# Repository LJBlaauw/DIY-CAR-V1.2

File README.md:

# DIY Robot CAR

**Dit project is begonnen met het idee van mijn zwager om een robot karretje te maken**
Ik heb zelf een achtergrond in ontwikkeling van elektronica (microcontrollers, vermogens-elektronica en audio).
Voor mijn zwager was dit onbekend gebied dus zoals wel vaker gebeurt heb ik mijn hulp aangeboden.
Voor de ontwikkeling is er gebruik gemaakt van opensource software. Als OS heb ik Linux Fedora 44 desktop KDE plasma gebruikt.
De uitdaging is om het karretje autonoom deze handelingen te laten uitvoeren, vooral het real-time karakter hierbij is een uitdaging.
Eerst hebben we alles op een breadboardje gebouwd. Dit was niet erg succesvol omdat de bedrading vaak geen betrouwbare verbindingen gaf.
Ook was de keuze van het type stappenmotor (unipolair) en servo's niet toereikend (te licht, te veel mechanische speling)
Dus versie nul is geüpdatet naar versie 1 met bipolaire stappenmotoren en drivers, MG996 servo's met metalen tandwielen.
Om dit te kunnen monteren zijn er diverse onderdelen 3D-geprint. 
In versie 1 was het grootste deel van de mechanica opgebouwd uit plaatmateriaal en aluminium profielen.
In versie 2 is er een elektronisch kompas en versnellingsopnemer toegevoegd. Ook is de grijper principieel gewijzigd en is zoveel als mogelijk 3D-geprint.

De eerste vragen die beantwoord moesten worden waren:
 1. Wat is de scope van het project (wat moet het robot karretje doen)
 2. Wat is goed online verkrijgbaar 
 3. Welke materialen gaan we gebruiken (motoren en sensoren)
 4. Wat voor software gaan we gebruiken om de besturing mogelijk te maken.
 5. presentatie van status en meet gegevens
 6. Ontwikkel gereedschappen en omgeving
 
1. **Scope: Het robot karretje moet autonoom zoeken naar een lichtbron en daar een voorwerp pakken en naar het vertrekpunt brengen**

2. **verkrijgbaarheid:**
 1. Bij diverse hobby winkels, amazon en aliexpress konden we alles wel vinden.
 
3. **Materialen**
 1. *Motoren:*
    1. Twee onafhankelijk te besturen stappenmotoren voor de voortbeweging.
    2. Drie onafhankelijk te besturen servomotoren voor de robotarm en grijper.
    *Sensoren:*
    1. Ultrasoonsensor om de afstand van de kar tot het object te meten.
    2. Twee licht gevoelige weerstanden om de richting van de lichtbron te vinden.
    3. We hebben als Microcontroller gekozen voor de RP2040 van Raspberry Pi, in versie 2 de RP2350W.
    4. Als optie een kompas/versnellings opnemer.
    5. Als optie een wifi koppeling met een websocket om sensor data te lezen en opdragten te geven.
    
 4. **Programmeertaal**
    Voor de programmeertaal hebben we gekozen voor Micropython dit is eenvoudiger te leren dan C/C++.
    Het voordeel is dat er niet vertaald hoeft te worden en er veel kant en klare bibliotheek componenten ingebouwd zijn.
    Om een goed real-time werkend systeem te krijgen zijn er wel een aantal uitdagingen.
    Aangezien Micropython een interpreter is loopt dit een factor 100 langzamer dan C.
    Er zijn een aantal mogelijkheden om de realtime eigenschappen te optimaliseren.
    1. Gebruik maken van de in de microcontroller geïntegreerde PIO-statemachines.
    2. De Software modules (werkbelasting) te verdelen over de twee CPU cores
    3. eventueel gebruik maken van de coöperatieve multitasking (asyncio).
    
5. **Presentatie**
    Als presentatie hebben we als status melding een meerkleuren LED en een oled display van 128x64 dots.
    Met versie twee hebben we gekozen voor de RP2350W. Deze heeft 2 M33 i.p.v de M0 kernen.
    Met deze processor update is het rekenen aan de kompas/versnellings veel sneller,
    ook is met een websocket remote besturing/uitlezing mogelijk. 
    Verder zijn er twee ledjes die de 5V en 3.3V signaleren.
    Hierbij is ook de REPL van de IDE gereedschappen aanwezig om met print opdrachten informatie te tonen.
    
6. **Ontwikkelgereedschappen**
    Voor het ontwerpen en produceren van de printplaat voor de elektronica maak ik gebruik van:
    1. Schema en layout: KiCAD (nu versie 10.4), FlatCAM Gerber naar Gcode, CNC machine een geüpgrade 3018 met GRBLHAL controller.
    2. Mechanisch ontwerp: FreeCAD voor 3D parametrische modellen en een Prusa MK4 3D-printer.
    3. Software ontwikkel omgeving: IDE VSCODE met micropico-extensie en AI claude 4.6 chat.
    4. Thonny IDE simpelere ontwikkelomgeving dan VSCODE.

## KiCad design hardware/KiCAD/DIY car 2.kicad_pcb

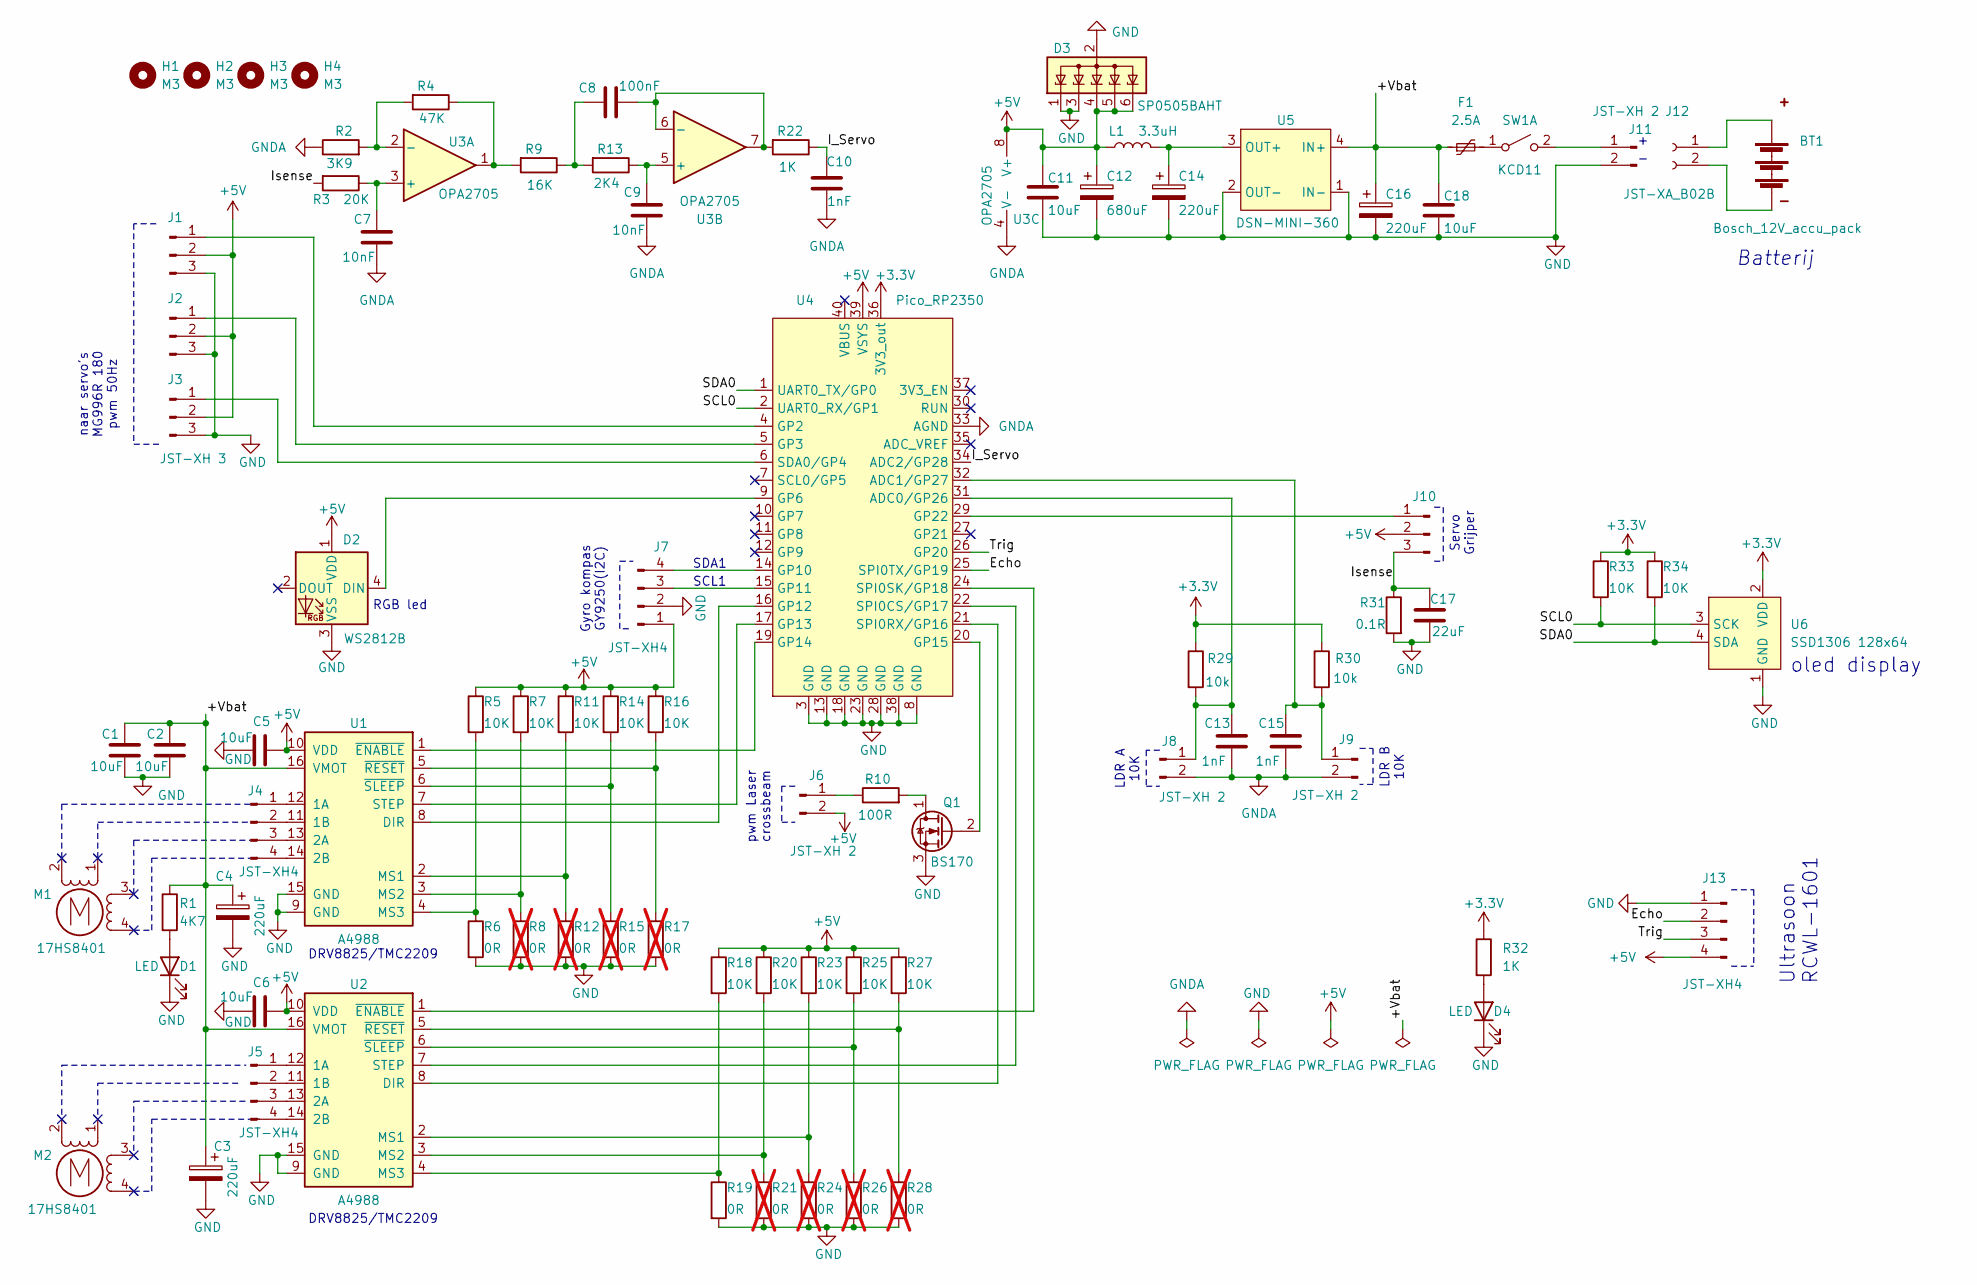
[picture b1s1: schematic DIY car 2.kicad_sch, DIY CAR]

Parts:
BT1: Bosch_12V_accu_pack; batterij houder bosch
C1, C2, C5, C6, C11, C18: 10uF; C_1206_3216Metric_Pad1.33x1.80mm_HandSolder
C3, C4, C14, C16: 220uF; CP_Radial_D6.3mm_P2.50mm
C7, C9: 10nF; C_1206_3216Metric_Pad1.33x1.80mm_HandSolder
C8: 100nF; C_1206_3216Metric_Pad1.33x1.80mm_HandSolder
C10, C13, C15: 1nF; C_1206_3216Metric_Pad1.33x1.80mm_HandSolder
C12: 680uF; CP_Radial_D8.0mm_P3.50mm
C17: 22uF; C_1210_3225Metric_Pad1.33x2.70mm_HandSolder
D1, D4: LED; LED_D3.0mm
D2: WS2812B; LED_WS2812B_PLCC4_5.0x5.0mm_P3.2mm
D3: SP0505BAHT; SOT-23-6
F1: 2.5A; Fuse_Bourns_MF-RG300
H1, H2, H3, H4: M3; MountingHole_3.5mm
J1, J2, J3, J10: JST-XH 3; JST_XH_B3B-XH-A_1x03_P2.50mm_Vertical
J4, J5, J7, J13: JST-XH4; JST_XH_B4B-XH-A_1x04_P2.50mm_Vertical
J6, J8, J9, J11: JST-XH 2; JST_XH_B2B-XH-AM_1x02_P2.50mm_Vertical_CNC
J12: JST-XA_B02B; JST_XA_B02B-XASK-1-A_1x02_P2.50mm_Vertical
L1: 3.3uH; L_APV_ANR6045
M1, M2: 17HS8401
Q1: BS170; TO-92_Inline
R1: 4K7; R_1206_3216Metric_Pad1.30x1.75mm_HandSolder
R2: 3K9; R_1206_3216Metric_Pad1.30x1.75mm_HandSolder
R3: 20K; R_1206_3216Metric_Pad1.30x1.75mm_HandSolder
R4: 47K; R_1206_3216Metric_Pad1.30x1.75mm_HandSolder
R5, R7, R11, R14, R16, R18, R20, R23, R25, R27, R33, R34: 10K; R_1206_3216Metric_Pad1.30x1.75mm_HandSolder
R6, R19: 0R; R_1206_3216Metric_Pad1.30x1.75mm_HandSolder
R8, R12, R15, R17, R21, R24, R26, R28: 0R; R_1206_3216Metric_Pad1.30x1.75mm_HandSolder; not fitted
R9: 16K; R_1206_3216Metric_Pad1.30x1.75mm_HandSolder
R10: 100R; R_1206_3216Metric_Pad1.30x1.75mm_HandSolder
R13: 2K4; R_1206_3216Metric_Pad1.30x1.75mm_HandSolder
R22, R32: 1K; R_1206_3216Metric_Pad1.30x1.75mm_HandSolder
R29, R30: 10k; R_1206_3216Metric_Pad1.30x1.75mm_HandSolder
R31: 0.1R; R_1020_2550Metric_Pad1.33x5.20mm_HandSolder
SW1: KCD11
U1, U2: A4988
U3: OPA2705; DIP-8_W7.62mm_Socket_LongPads
U4: Pico_RP2350; DIP-40_700mil
U5: DSN-MINI-360
U6: SSD1306 128x64; OLED 0.96 I2C

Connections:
+3.3V: R29.1, R30.1, R32.1, R33.1, R34.1, U4.36 (3V3_out), U6.2 (VDD)
+5V: C5.2, C6.2, C11.2, C12.1, D2.1 (VDD), D3.4 (K), D3.5 (K), D3.6 (K), J1.2, J2.2, J3.2, J6.2, J7.1, J10.2, J13.4, L1.1, R5.1, R7.1, R11.1, R14.1, R16.1, R18.1, R20.1, R23.1, R25.1, R27.1, U1.10 (VDD), U2.10 (VDD), U3.8 (V+), U4.39 (VSYS)
/+Vbat: C1.2, C2.2, C3.1, C4.1, C16.1, C18.2, F1.1, R1.1, U1.16 (VMOT), U2.16 (VMOT), U5.4 (IN+)
/Echo: J13.2, U4.25 (SPI0TX/GP19)
/I_Servo: C10.2, R22.1, U4.34 (ADC2/GP28)
/Isense: C17.1, J10.3, R3.2, R31.1
/SCL0: R33.2, U4.2 (UART0_RX/GP1), U6.3 (SCK)
/SDA0: R34.2, U4.1 (UART0_TX/GP0), U6.4 (SDA)
/Trig: J13.3, U4.26 (GP20)
GND: C1.1, C2.1, C3.2, C4.2, C5.1, C6.1, C11.1, C12.2, C14.2, C16.2, C17.2, C18.1, D1.1 (K), D2.3 (VSS), D3.1 (K), D3.2 (A), D3.3 (K), D4.1 (K), J1.3, J2.3, J3.3, J7.2, J11.2, J13.1, Q1.3 (S), R6.2, R8.2, R12.2, R15.2, R17.2, R19.2, R21.2, R24.2, R26.2, R28.2, R31.2, U1.9 (GND), U1.15 (GND), U2.9 (GND), U2.15 (GND), U4.3 (GND), U4.8 (GND), U4.13 (GND), U4.18 (GND), U4.23 (GND), U4.28 (GND), U4.38 (GND), U5.1 (IN-), U5.2 (OUT-), U6.1 (GND)
GNDA: C7.1, C9.1, C10.1, C13.1, C15.1, J8.2, J9.2, R2.1, U3.4 (V-), U4.33 (AGND)
unnamed: BT1.1 (+), J12.1
unnamed: BT1.2 (-), J12.2
unnamed: C8.1, R9.1, R13.2
unnamed: D1.2 (A), R1.2
unnamed: D2.4 (DIN), U4.9 (GP6)
unnamed: D4.2 (A), R32.2
unnamed: J1.1, U4.4 (GP2)
unnamed: J2.1, U4.5 (GP3)
unnamed: J3.1, U4.6 (SDA0/GP4)
unnamed: J4.1, U1.12 (1A)
unnamed: J4.2, U1.11 (1B)
unnamed: J4.3, U1.13 (2A)
unnamed: J4.4, U1.14 (2B)
unnamed: J5.1, U2.12 (1A)
unnamed: J5.2, U2.11 (1B)
unnamed: J5.3, U2.13 (2A)
unnamed: J5.4, U2.14 (2B)
unnamed: J6.1, R10.1
unnamed: J7.3, U4.15 (GP11)
unnamed: J7.4, U4.14 (GP10)
unnamed: C13.2, J8.1, R29.2, U4.31 (ADC0/GP26)
unnamed: C15.2, J9.1, R30.2, U4.32 (ADC1/GP27)
unnamed: J10.1, U4.29 (GP22)
unnamed: J11.1, SW1.2 (B)
unnamed: Q1.1 (D), R10.2
unnamed: Q1.2 (G), U4.20 (GP15)
unnamed: R4.1, R9.2, U3.1
unnamed: F1.2, SW1.1 (A)
unnamed: U1.8 (DIR), U4.16 (GP12)
unnamed: R11.2, R12.1, U1.2 (MS1)
unnamed: R7.2, R8.1, U1.3 (MS2)
unnamed: R5.2, R6.1, U1.4 (MS3)
unnamed: U1.7 (STEP), U4.17 (GP13)
unnamed: U1.1 (~ENABLE), U4.19 (GP14)
unnamed: R16.2, R17.1, U1.5 (~RESET)
unnamed: R14.2, R15.1, U1.6 (~SLEEP)
unnamed: U2.8 (DIR), U4.21 (SPI0RX/GP16)
unnamed: R23.2, R24.1, U2.2 (MS1)
unnamed: R20.2, R21.1, U2.3 (MS2)
unnamed: R18.2, R19.1, U2.4 (MS3)
unnamed: U2.7 (STEP), U4.22 (SPI0CS/GP17)
unnamed: U2.1 (~ENABLE), U4.24 (SPI0SK/GP18)
unnamed: R27.2, R28.1, U2.5 (~RESET)
unnamed: R25.2, R26.1, U2.6 (~SLEEP)
unnamed: C7.2, R3.1, U3.3 (+)
unnamed: R2.2, R4.2, U3.2 (-)
unnamed: C9.2, R13.1, U3.5 (+)
unnamed: C8.2, R22.2, U3.6 (-), U3.7
unnamed: C14.1, L1.2, U5.3 (OUT+)

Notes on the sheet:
oled display
LDR B 10K
DRV8825/TMC2209
SCL1
pwm Laser crossbeam
Ultrasoon RCWL-1601
Gyro kompas GY9250(I2C)
naar servo's MG996R 180 pwm 50Hz
RGB led
SDA1
Servo Grijper
LDR A 10K
Batterij

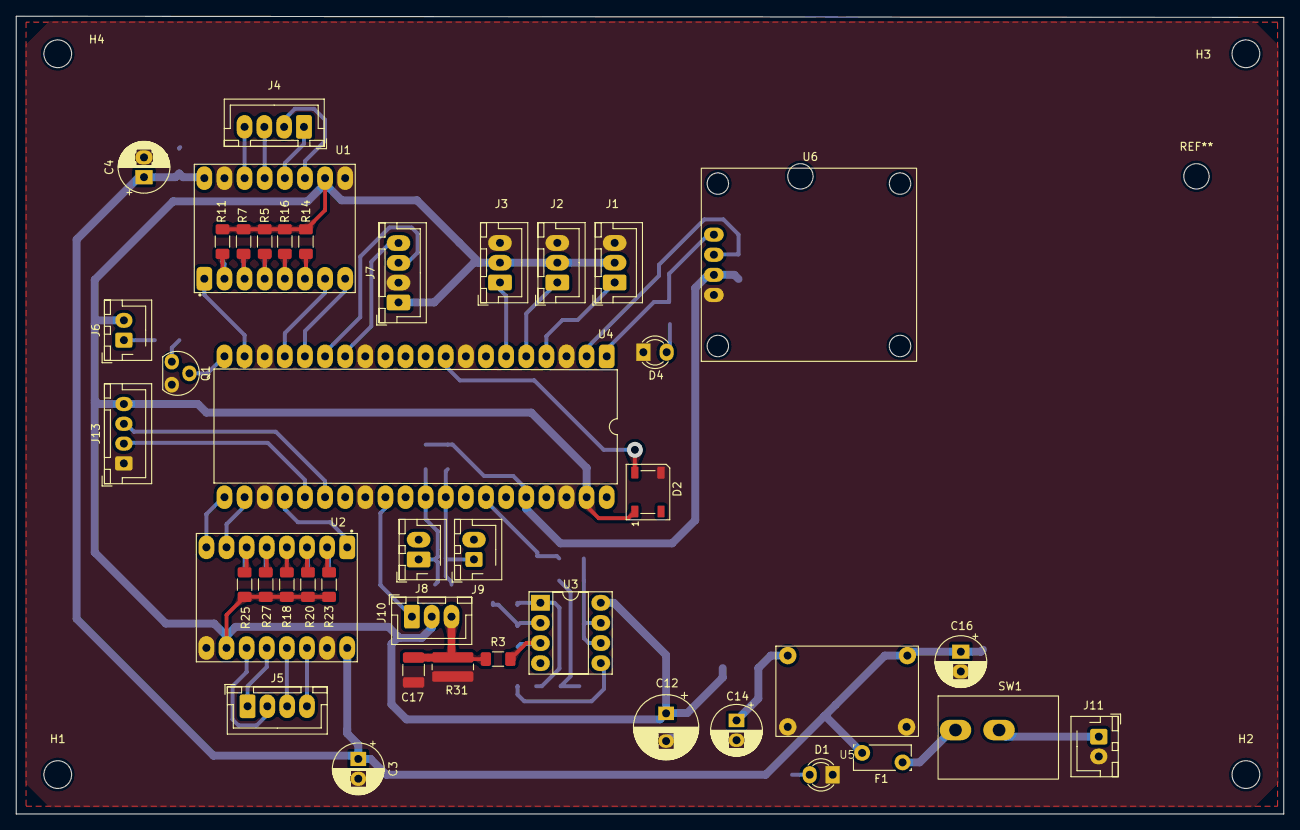
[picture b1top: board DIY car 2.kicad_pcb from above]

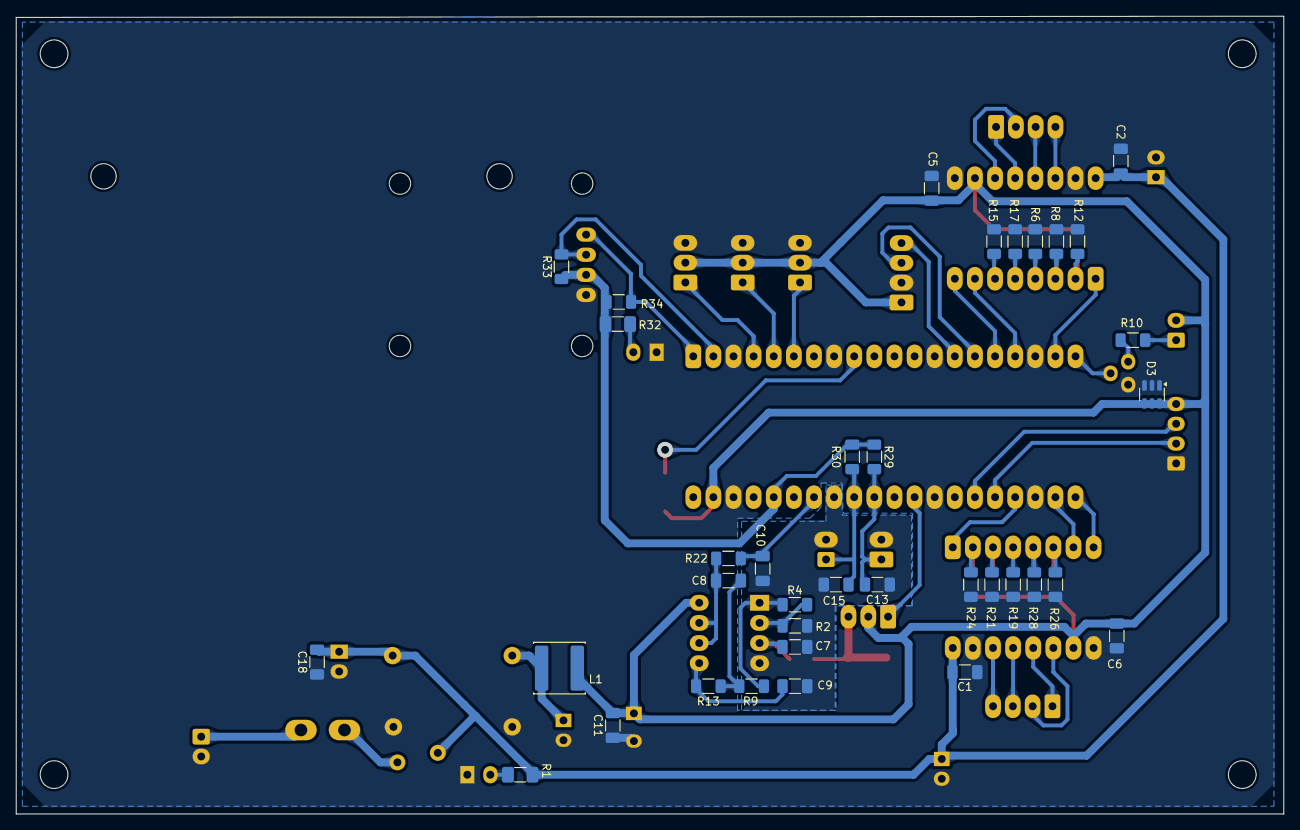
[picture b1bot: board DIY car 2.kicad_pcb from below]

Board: 2 copper layers, 160.0 x 100.7 mm, 82 parts (36 on the bottom side), 58 nets.

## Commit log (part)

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2026-01-19 Eerste commit
2026-01-26 added stepper *.md
2026-06-09 Update DIY CAR v1.2 updated for RP2350
